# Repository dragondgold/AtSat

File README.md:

<h2>
</a>Desarrollo de satélite CanSat para
utilizar como plataforma educativa y
fomentar el interés en ingenierías</h2>

El objetivo principal del proyecto es el de proveer un satélite tipo CanSat completamente funcional y listo para ser utilizado, 
con una Estación Terrena para la comunicación con el mismo, a modo de plataforma educativa que permite no solo ser utilizada 
por estudiantes sin modificación alguna, sino que provee la capacidad de ser expandida para agregar o mejorar las funcionalidades 
básicas dando lugar a los estudiantes a experimentar libremente sobre una plataforma segura.

A su vez, la plataforma sera diseñada siguiendo la normativa impuesta por la European Space Agency (ESA) 
lo cual dará la posibilidad a futuro de participar de competencias de CanSat.

El proyecto está pensado para que el CanSat pueda alcanzar una altura máxima de
1000 metros aproximadamente y realice un descenso con la ayuda de un paracaídas que
limitará su velocidad para evitar la destrucción del mismo al impactar contra el suelo.
Durante esta etapa también se realizará la medición de las variables
que envía el CanSat a la Estación Terrena para luego ser interpretadas. Esto permite
analizar diversos factores respecto a la altura como los niveles de contaminación del
aire, la variabilidad de la temperatura y presión atmosférica, la toma de imágenes para
su posterior procesamiento, medición de radiación UV, composición gaseosa del aire,
etcétera.

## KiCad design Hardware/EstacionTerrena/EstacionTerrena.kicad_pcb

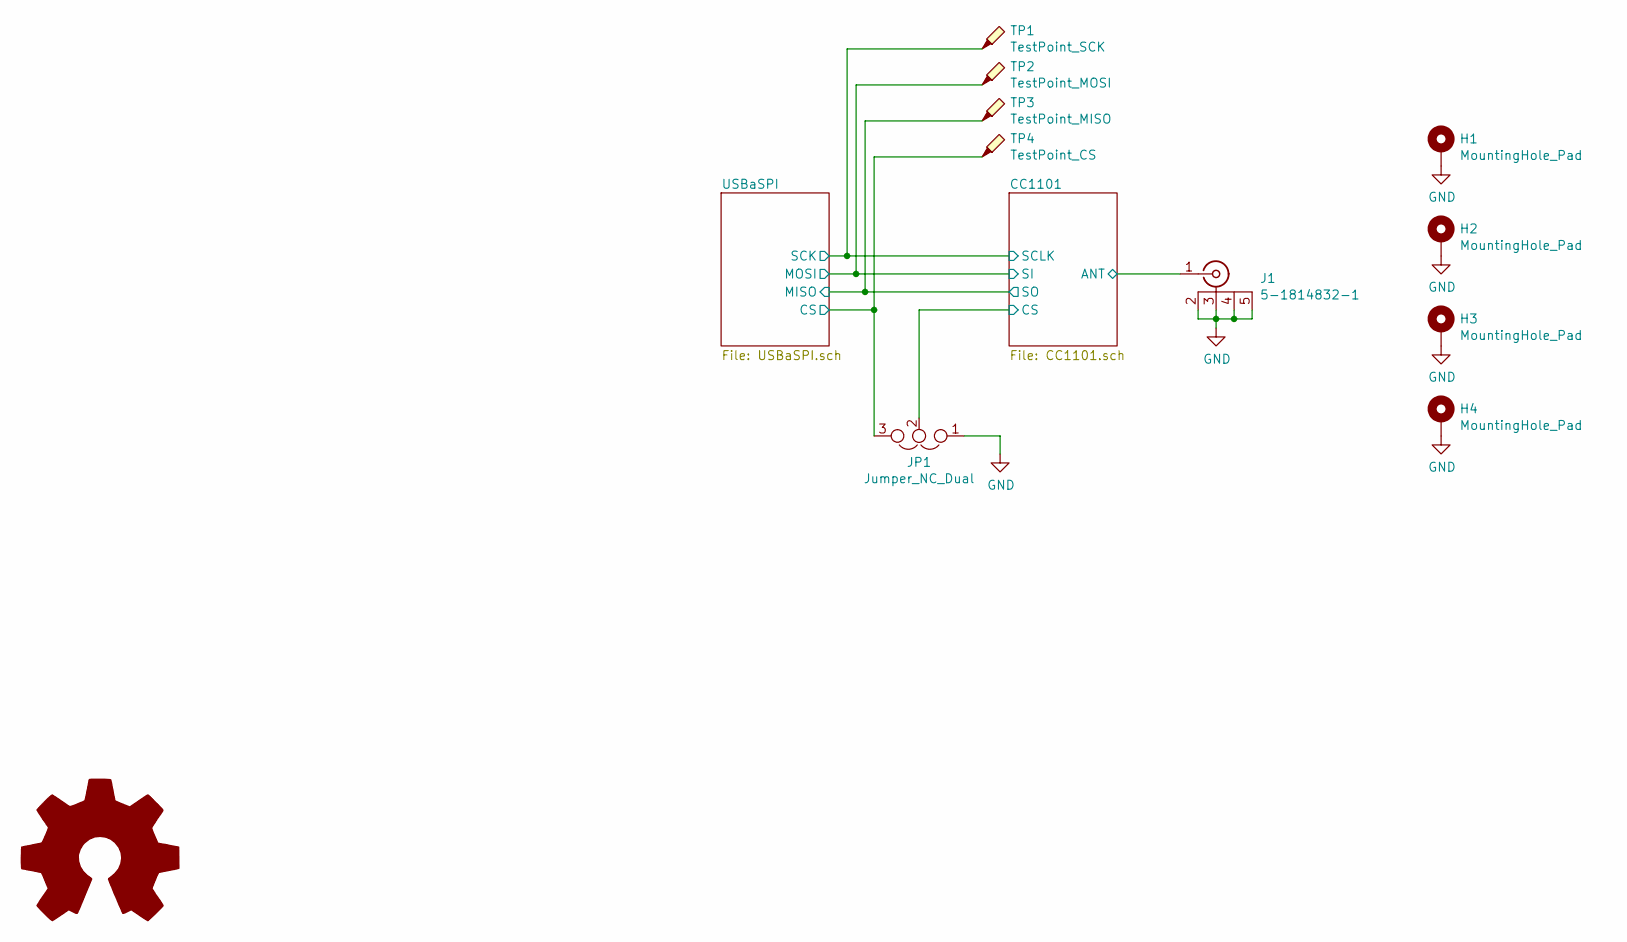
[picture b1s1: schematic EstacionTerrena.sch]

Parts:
H1, H2, H3, H4: MountingHole_Pad; MountingHole_3.2mm_M3_Pad
J1: 5-1814832-1; Manufacturer Part Number 5-1814832-1
JP1: Jumper_NC_Dual; SolderJumper-3_P1.3mm_Open_RoundedPad1.0x1.5mm_NumberLabels
TP1: TestPoint_SCK; TestPoint_Pad_D1.0mm
TP2: TestPoint_MOSI; TestPoint_Pad_D1.0mm
TP3: TestPoint_MISO; TestPoint_Pad_D1.0mm
TP4: TestPoint_CS; TestPoint_Pad_D1.0mm

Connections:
/CC1101/ANT: J1.1; also elsewhere on the board
/CC1101/CS: JP1.2; also elsewhere on the board
/USBaSPI/CS: JP1.3, TP4.1; also elsewhere on the board
/USBaSPI/MISO: TP3.1; also elsewhere on the board
/USBaSPI/MOSI: TP2.1; also elsewhere on the board
/USBaSPI/SCK: TP1.1; also elsewhere on the board
GND: H1.1, H2.1, H3.1, H4.1, J1.2, J1.3, J1.4, J1.5, JP1.1; also elsewhere on the board

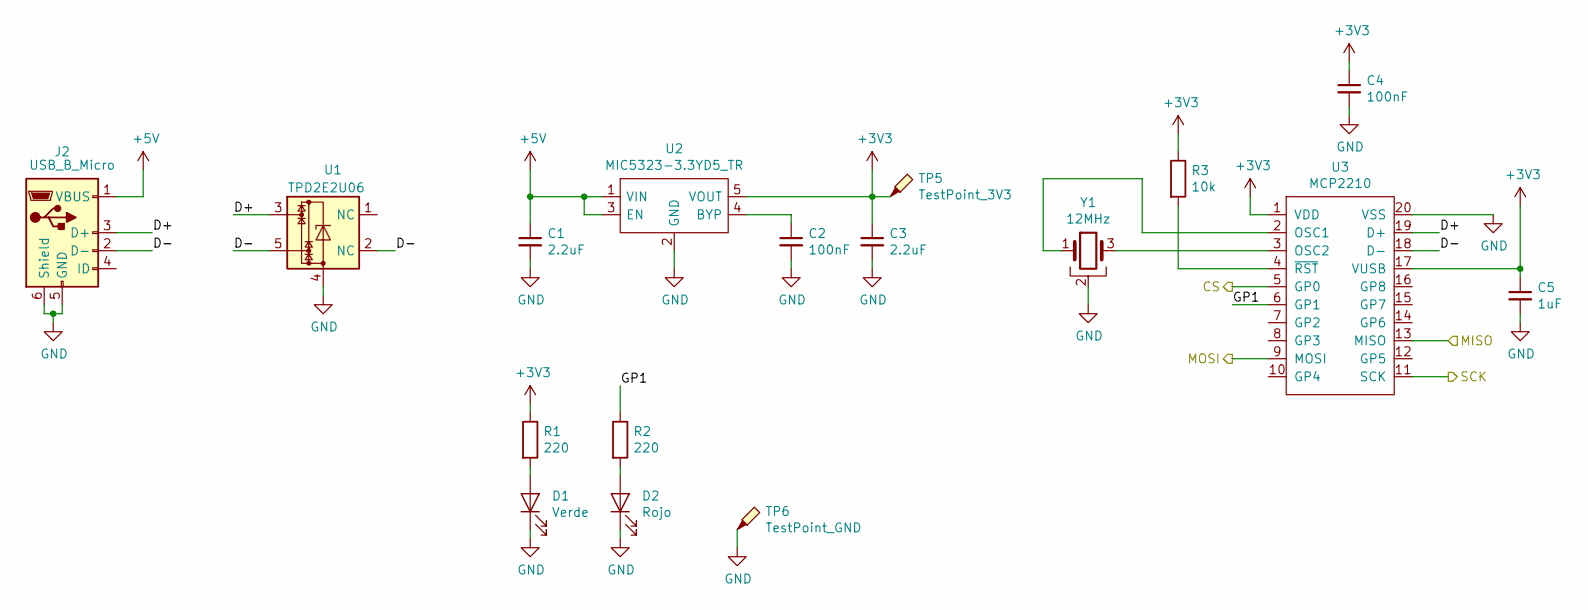
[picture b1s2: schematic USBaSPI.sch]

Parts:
C1, C3: 2.2uF; C_0805_2012Metric; Voltage 10V; Manufacturer Part Number LMK212B7225KG-T
C2, C4: 100nF; C_0603_1608Metric; Voltage 16V; Manufacturer Part Number EMK107B7104KAHT
C5: 1uF; C_0603_1608Metric; Voltage 10V; Manufacturer Part Number LMK107B7105MA-T
D1: Verde; LED_0603_1608Metric; Manufacturer Part Number 150060VS75000
D2: Rojo; LED_0603_1608Metric; Manufacturer Part Number 150060RS75000
J2: USB_B_Micro; USB_Micro-B_Molex-105017-0001; Manufacturer Part Number 105017-0001
R1, R2: 220; R_0603_1608Metric_Pad1.05x0.95mm_HandSolder; Manufacturer Part Number RC0603JR-13220RL
R3: 10k; R_0603_1608Metric_Pad1.05x0.95mm_HandSolder; Manufacturer Part Number RC0603JR-0710KL
TP5: TestPoint_3V3; TestPoint_Pad_D1.0mm
TP6: TestPoint_GND; TestPoint_THTPad_1.0x1.0mm_Drill0.5mm
U1: TPD2E2U06; SOT-553; Manufacturer Part Number TPD2E2U06DRLR
U2: MIC5323-3.3YD5_TR; SOT95P280X100-5N; Manufacturer Part Number MIC5323-3.3YD5 TR
U3: MCP2210; SSOP-20_5.3x7.2mm_P0.65mm; Manufacturer Part Number MCP2210-I/SS
Y1: 12MHz; Resonator_SMD_muRata_CSTxExxV-3Pin_3.0x1.1mm; Manufacturer Part Number CSTNE12M0GH5L000R0

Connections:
+3V3: C3.1, C4.1, C5.1, R1.1, R3.1, TP5.1, U2.5 (VOUT), U3.1 (VDD), U3.17 (VUSB); also elsewhere on the board
+5V: C1.1, J2.1 (VBUS), U2.1 (VIN), U2.3 (EN)
/USBaSPI/CS: U3.5 (GP0); also elsewhere on the board
/USBaSPI/D+: J2.3 (D+), U1.3, U3.19 (D+)
/USBaSPI/D-: J2.2 (D-), U1.2 (NC), U1.5, U3.18 (D-)
/USBaSPI/GP1: R2.1, U3.6 (GP1)
/USBaSPI/MISO: U3.13 (MISO); also elsewhere on the board
/USBaSPI/MOSI: U3.9 (MOSI); also elsewhere on the board
/USBaSPI/SCK: U3.11 (SCK); also elsewhere on the board
GND: C1.2, C2.2, C3.2, C4.2, C5.2, D1.1 (K), D2.1 (K), J2.5 (GND), J2.6 (Shield), TP6.1, U1.4, U2.2 (GND), U3.20 (VSS), Y1.2; also elsewhere on the board
unnamed: C2.1, U2.4 (BYP)
unnamed: D1.2 (A), R1.2
unnamed: D2.2 (A), R2.2
unnamed: R3.2, U3.4 (~RST)
unnamed: U3.2 (OSC1), Y1.1
unnamed: U3.3 (OSC2), Y1.3

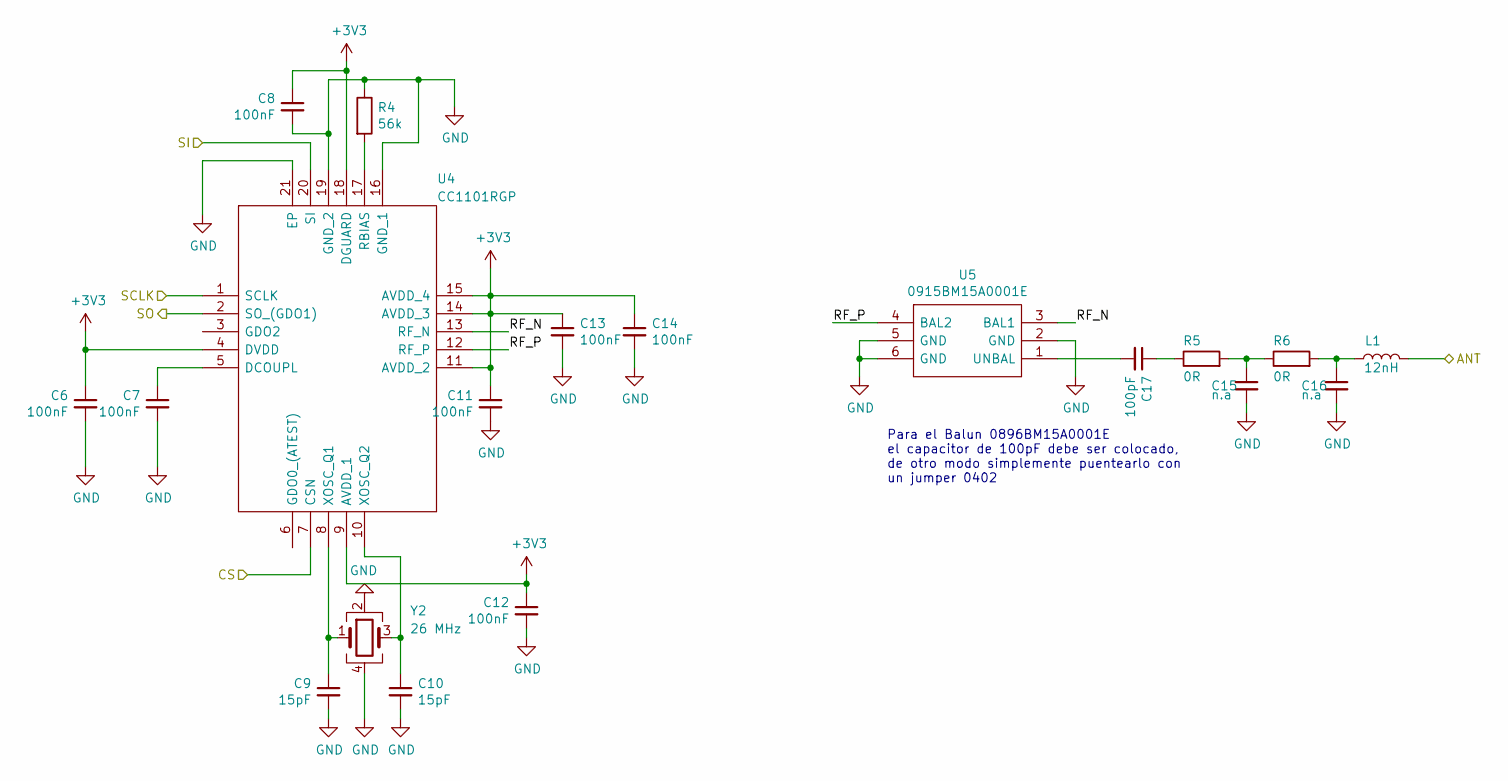
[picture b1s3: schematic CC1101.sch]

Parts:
C6, C7, C8, C11, C12, C13, C14: 100nF; C_0402_1005Metric; Voltage 16V; Manufacturer Part Number GCM155R71C104KA55D
C9, C10: 15pF; C_0402_1005Metric; Voltage 10V; Manufacturer Part Number C0402C150J5GACTU
C15, C16: n.a; C_0402_1005Metric
C17: 100pF; C_0402_1005Metric; Voltage 25V; Manufacturer Part Number 885012005046
L1: 12nH; L_0402_1005Metric; Manufacturer Part Number L-07C12NJV6
R4: 56k; R_0402_1005Metric; Manufacturer Part Number RC0402FR-0756KL
R5, R6: 0R; R_0402_1005Metric; Manufacturer Part Number RC0402JR-070RL
U4: CC1101RGP; QFN50P400X400X100-21N-D; Manufacturer Part Number CC1101RGP
U5: 0915BM15A0001E; Manufacturer Part Number 0915BM15A0001E
Y2: 26 MHz; Crystal_SMD_2520-4Pin_2.5x2.0mm; Manufacturer Part Number FA-20H 26.0000MF12V-W

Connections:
+3V3: C6.1, C8.1, C11.1, C12.1, C13.1, C14.1, U4.4 (DVDD), U4.9 (AVDD_1), U4.11 (AVDD_2), U4.14 (AVDD_3), U4.15 (AVDD_4), U4.18 (DGUARD); also elsewhere on the board
/CC1101/ANT: L1.2; also elsewhere on the board
/CC1101/CS: U4.7 (CSN); also elsewhere on the board
/CC1101/RF_N: U4.13 (RF_N), U5.3 (BAL1)
/CC1101/RF_P: U4.12 (RF_P), U5.4 (BAL2)
/USBaSPI/MISO: U4.2 (SO_(GDO1)); also elsewhere on the board
/USBaSPI/MOSI: U4.20 (SI); also elsewhere on the board
/USBaSPI/SCK: U4.1 (SCLK); also elsewhere on the board
GND: C6.2, C7.2, C8.2, C9.2, C10.2, C11.2, C12.2, C13.2, C14.2, C15.2, C16.2, R4.1, U4.16 (GND_1), U4.19 (GND_2), U4.21 (EP), U5.2 (GND), U5.5 (GND), U5.6 (GND), Y2.2, Y2.4; also elsewhere on the board
unnamed: C7.1, U4.5 (DCOUPL)
unnamed: C9.1, U4.8 (XOSC_Q1), Y2.1
unnamed: C10.1, U4.10 (XOSC_Q2), Y2.3
unnamed: C15.1, R5.2, R6.1
unnamed: C16.1, L1.1, R6.2
unnamed: C17.1, R5.1
unnamed: C17.2, U5.1 (UNBAL)
unnamed: R4.2, U4.17 (RBIAS)

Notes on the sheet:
Para el Balun 0896BM15A0001E el capacitor de 100pF debe ser colocado, de otro modo simplemente puentearlo con un jumper 0402

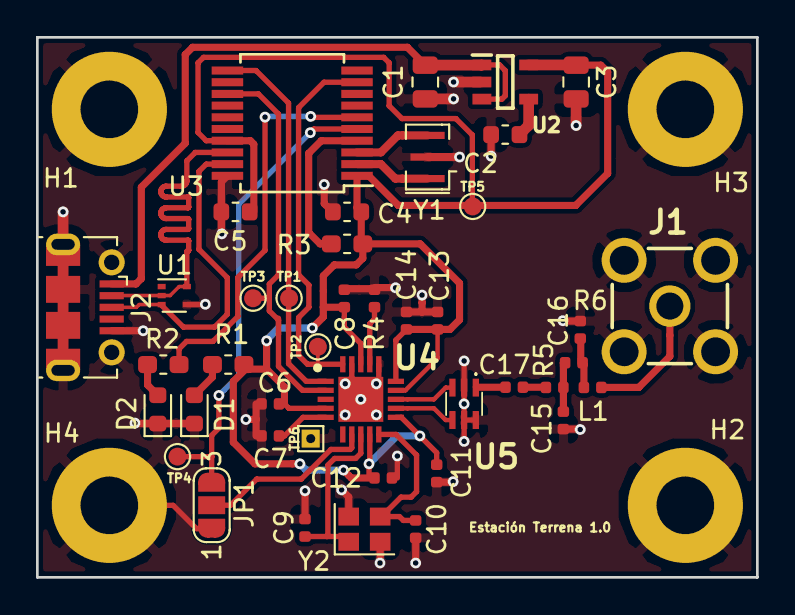
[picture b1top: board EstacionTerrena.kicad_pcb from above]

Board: 2 copper layers, 40.0 x 30.0 mm, 46 parts (0 on the bottom side), 28 nets.

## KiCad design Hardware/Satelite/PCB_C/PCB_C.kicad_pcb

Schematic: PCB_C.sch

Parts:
C1, C13: 1uF; C_0402_1005Metric; Manufacturer Part Number GRM155R61E105KA12D
C2, C5, C6, C9, C10, C11, C12, C14, C18, C19, C21: 100nF; C_0402_1005Metric; Manufacturer Part Number GCM155R71C104KA55D
C3, C4: 4.3pF; C_0402_1005Metric; Manufacturer Part Number GRM1555C1H4R3WA01D
C7, C8: 20pF; C_0402_1005Metric; Manufacturer Part Number GCM1555C1H200JA16D
C20: 4.7uF; C_0805_2012Metric_Pad1.15x1.40mm_HandSolder; Manufacturer Part Number GRM21BR71A475KE51K
IC1: MCP1501T-33E_CHY; SOT95P270X145-6N; Manufacturer Part Number MCP1501T-33E/CHY
IC2: IS25LP080D-JULE-TR; SON50P200X300X60-8N; Manufacturer Part Number IS25LP080D-JULE-TR
IC3: BQ24392RSER; RSE(R-PUQFN-N10); Manufacturer Part Number BQ24392RSER
J1: Conn_01x06; PinHeader_1x06_P2.54mm_Vertical; Manufacturer Part Number 68000-406HLF
J2: BOOT; PinHeader_1x03_P2.54mm_Vertical; Manufacturer Part Number 61300311121
J3: Conector_PCB_B-C; Conector_PCB_B-C_Lado_C; Manufacturer Part Number 10132797-025100LF
J4: Conector_Expansion_CanSat; Manufacturer Part Number SSQ-106-03-T-S
J5: USB_B_Micro; USB_Micro-B_Molex-105017-0001; Manufacturer Part Number 105017-0001
JP1: BOM_Jumper; Empty_Footprint; Manufacturer Part Number M7581-05
M1, M2, M3: Spacer; Empty_Footprint; Manufacturer Part Number R30-3011002
MH1: MH_CanSat
R1, R2, R3, R4: 10k; R_0603_1608Metric_Pad1.05x0.95mm_HandSolder; Manufacturer Part Number RC0603JR-0710KL
U1, U4: NTB0104BQ,115; NTB0104BQ115; Manufacturer Part Number NTB0104BQ,115
U2: TCA9802DGKR; SOP65P490X110-8N; Manufacturer Part Number TCA9802DGKR
U3: STM32F303RETx; LQFP-64_10x10mm_P0.5mm
Y1: LFXTAL016178; LFXTAL016178_1; Manufacturer Part Number LFXTAL016178
Y2: Crystal; Crystal_HC49-4H_Vertical; Manufacturer Part Number LFXTAL029665

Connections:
+3V3: C5.1, C11.1, C21.1, J3.4, J3.17, J4.14, U1.14, U2.8, U4.14; also elsewhere on the board
+3V3_Internal: C2.1, C9.1, C10.1, C12.1, C13.2, C14.1, C18.1, C19.1, C20.2, IC2.3, IC2.7, IC2.8, J1.1, J2.3, J3.10, R1.1, R2.1, R3.1, R4.1, U1.1, U2.1, U3.1 (VBAT), U3.19 (VDD), U3.32 (VDD), U3.48 (VDD), U3.64 (VDD), U4.1
+5V: J3.5, J3.13, J4.15
+BATT: C1.2, IC1.4, IC1.6, J3.6, J3.7, J3.8, J3.9, J4.13
/3V_ENABLE: J3.18, U3.26 (PB0)
/5V_ENABLE: J3.14, U3.23 (PA7)
/+VREF: IC1.1, U3.13 (VDDA)
/CHG: J3.29, U3.61 (PB8)
/CHG_ALLOWED: IC3.4, U3.27 (PB1)
/CHG_DETECT: IC3.10, U3.16 (PA2)
/CHG_DISABLE: J3.28, U3.54 (PD2)
/CS: J3.36, U3.33 (PB12), U4.5
/D+: IC3.3, U3.45 (PA12)
/D-: IC3.2, U3.44 (PA11)
/EXT_CS: J4.22, U4.10
/EXT_IO0: J4.3, U1.13
/EXT_IO1: J4.4, U1.12
/EXT_IO2: J4.5, U1.11
/EXT_IO3: J4.6, U1.10
/EXT_SCLK: J4.21, U4.11
/EXT_SDI: J4.20, U4.12
/EXT_SDO: J4.19, U4.13
/FLASH_CS: IC2.1, U3.2 (PC13)
/FLASH_MISO: IC2.2, U3.52 (PC11)
/FLASH_MOSI: IC2.5, U3.53 (PC12)
/FLASH_SCK: IC2.6, U3.51 (PC10)
/GPOUT: J3.24, U3.57 (PB5)
/GPS_TX: J3.20, U3.56 (PB4)
/I2C_EN: U2.5, U3.24 (PC4)
/IO0: U1.2, U3.10 (PC2)
/IO1: U1.3, U3.11 (PC3)
/IO2: U1.4, U3.29 (PB10)
/IO3: U1.5, U3.30 (PB11)
/IO_EN: U1.8, U3.39 (PC8)
/ISET: J3.30, U3.62 (PB9)
/I_SENSE_3V3: J3.16, U3.15 (PA1)
/I_SENSE_5V: J3.12, U3.14 (PA0)
/I_SENSE_BATT: J3.31, U3.17 (PA3)
/NRST: C6.1, J1.5, U3.7 (NRST)
/P1: J3.19, U3.59 (PB7)
/SCL: R3.2, U2.3, U3.42 (PA9); also elsewhere on the board
/SCLK: J3.35, U3.34 (PB13), U4.4
/SCL_CHG: J3.25, R2.2, U3.41 (PA8)
/SCL_EXT: J4.23, U2.6
/SDA: R4.2, U2.2, U3.43 (PA10); also elsewhere on the board
/SDA_CHG: J3.26, R1.2, U3.40 (PC9)
/SDA_EXT: J4.24, U2.7
/SDI: J3.37, U3.36 (PB15), U4.3
/SDO: J3.34, U3.35 (PB14), U4.2
/SPI_BUFFER_EN: U3.25 (PC5), U4.8
/SWCLK: J1.2, U3.49 (PA14)
/SWDIO: J1.4, U3.46 (PA13)
/SWO: J1.6, U3.55 (PB3)
/SW_OPEN: IC3.1, U3.28 (PB2)
/S_GLOBO: J3.32, U3.8 (PC0)
/S_PARACAIDAS: J3.33, U3.9 (PC1)
/V_SENSE_3V3: J3.15, U3.20 (PA4)
/V_SENSE_5V: J3.11, U3.21 (PA5)
GND: C1.1, C2.2, C3.2, C4.2, C5.2, C6.2, C7.2, C8.2, C9.2, C10.2, C11.2, C12.2, C13.1, C14.2, C18.2, C19.2, C20.1, C21.2, IC1.2, IC1.3, IC1.5, IC2.4, IC3.6, J1.3, J2.1, J3.1, J3.2, J3.3, J3.21, J3.22, J3.23, J3.38, J3.39, J3.40, J4.16, J4.17, J4.18, J5.5, J5.6, MH1.1, MH1.2, MH1.3, U1.7, U1.15, U2.4, U3.12 (VSSA), U3.18 (VSS), U3.31 (VSS), U3.47 (VSS), U3.63 (VSS), U4.7, U4.15; also elsewhere on the board
unnamed: C3.1, U3.3 (PC14), Y1.1
unnamed: C4.1, U3.4 (PC15), Y1.4
unnamed: C7.1, U3.5 (PF0), Y2.1
unnamed: C8.1, U3.6 (PF1), Y2.2
unnamed: IC3.7, J5.3
unnamed: IC3.8, J5.2
unnamed: J2.2, U3.60 (BOOT0)
VBUS: IC3.5, IC3.9, J3.27, J5.1

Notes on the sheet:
USB y detección de cargador
Sensores
+VREF ADC
Header programación
Buffer SPI
Buffer I2C
Buffer IO_A
Conectores a PCB_B
Conector de expansión
AGUJEROS DE MONTAJE
Mecánica

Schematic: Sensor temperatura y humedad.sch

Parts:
C22: 100nF; C_0402_1005Metric; Manufacturer Part Number GCM155R71C104KA55D
U6: Si7006-A20-IM1; SON100P300X300X80-7N; Manufacturer Part Number Si7006-A20-IM1

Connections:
+3V3: C22.1, U6.5; also elsewhere on the board
/SCL: U6.6; also elsewhere on the board
/SDA: U6.1; also elsewhere on the board
GND: C22.2, U6.2; also elsewhere on the board

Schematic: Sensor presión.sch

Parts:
C23: 1uF; C_0402_1005Metric; Manufacturer Part Number GRM155R61E105KA12D
IC4: MS563702BA03-50; MS5637_1; Manufacturer Part Number MS563702BA03-50

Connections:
+3V3: C23.2, IC4.1; also elsewhere on the board
/SCL: IC4.3; also elsewhere on the board
/SDA: IC4.2; also elsewhere on the board
GND: C23.1, IC4.4; also elsewhere on the board

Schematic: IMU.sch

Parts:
C24, C25: 100nF; C_0402_1005Metric; Manufacturer Part Number GCM155R71C104KA55D
IC5: BMX055; LGA_PACKAGE_20_PINS; Manufacturer Part Number BMX055

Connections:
+3V3: C24.1, C25.1, IC5.3, IC5.7, IC5.13; also elsewhere on the board
/IMU/ACC_INT: IC5.1
/IMU/GYRO_INT: IC5.14
/IMU/MAG_INT: IC5.10
/SCL: IC5.9; also elsewhere on the board
/SDA: IC5.11; also elsewhere on the board
GND: C24.2, C25.2, IC5.4, IC5.6, IC5.12, IC5.17, IC5.20; also elsewhere on the board

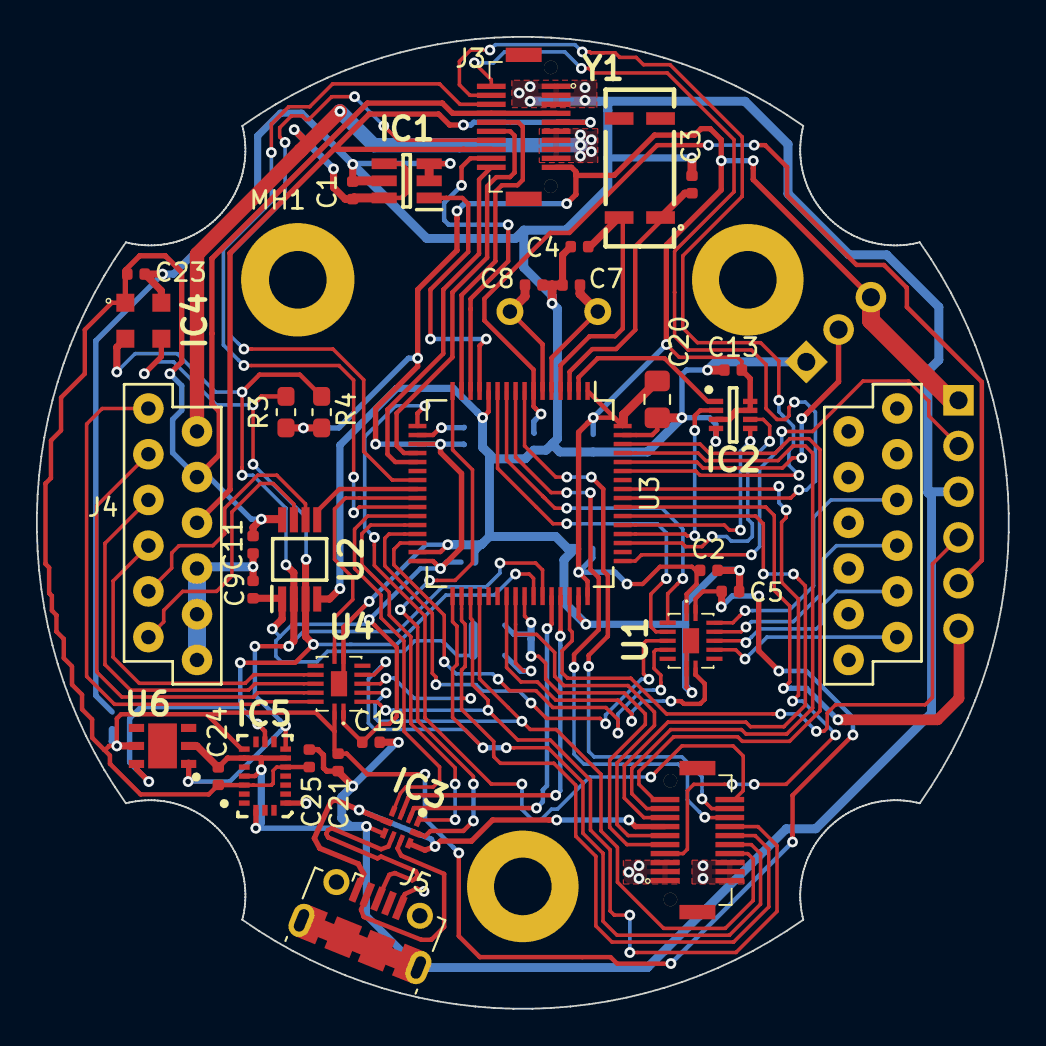
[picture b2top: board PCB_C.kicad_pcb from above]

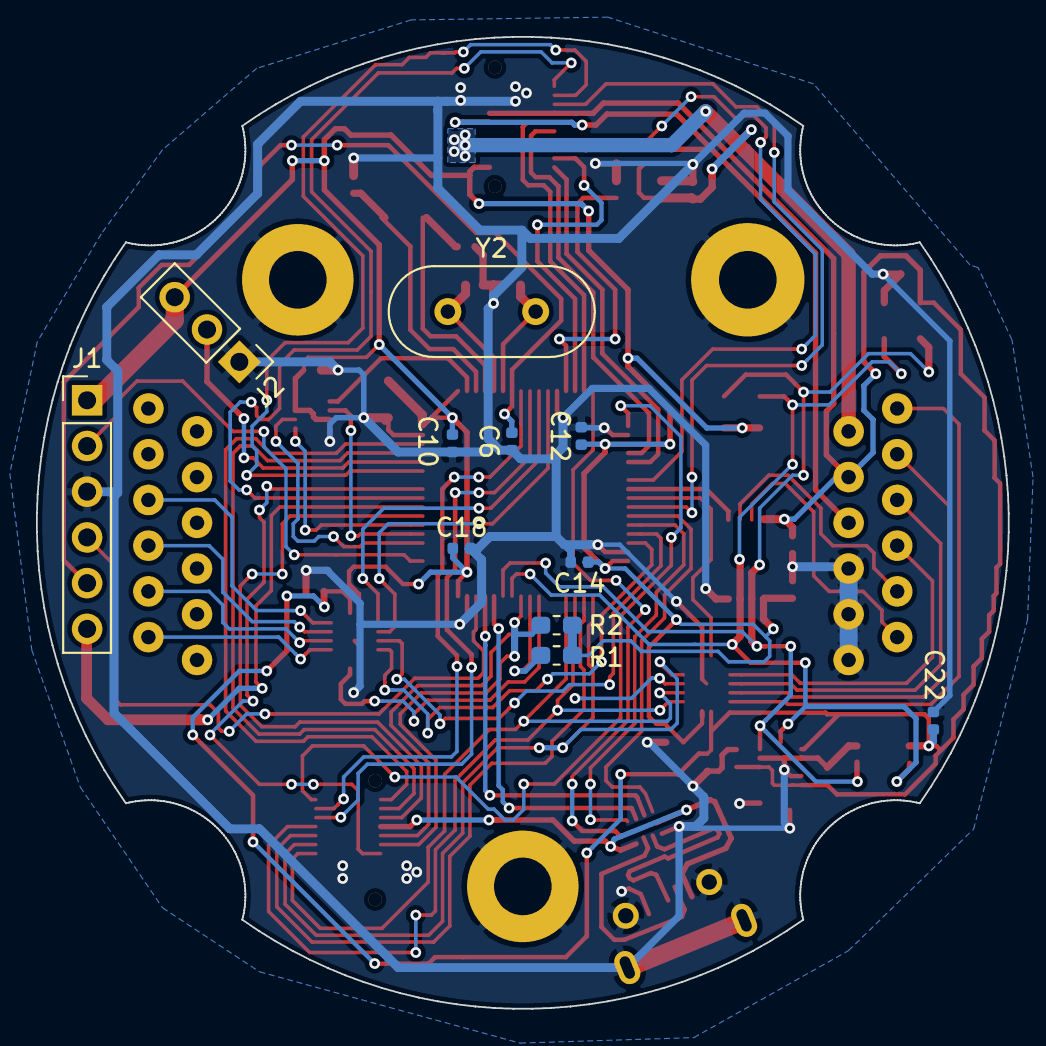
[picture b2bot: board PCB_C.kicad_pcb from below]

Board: 2 copper layers, 54.0 x 54.0 mm, 48 parts (11 on the bottom side), 67 nets.

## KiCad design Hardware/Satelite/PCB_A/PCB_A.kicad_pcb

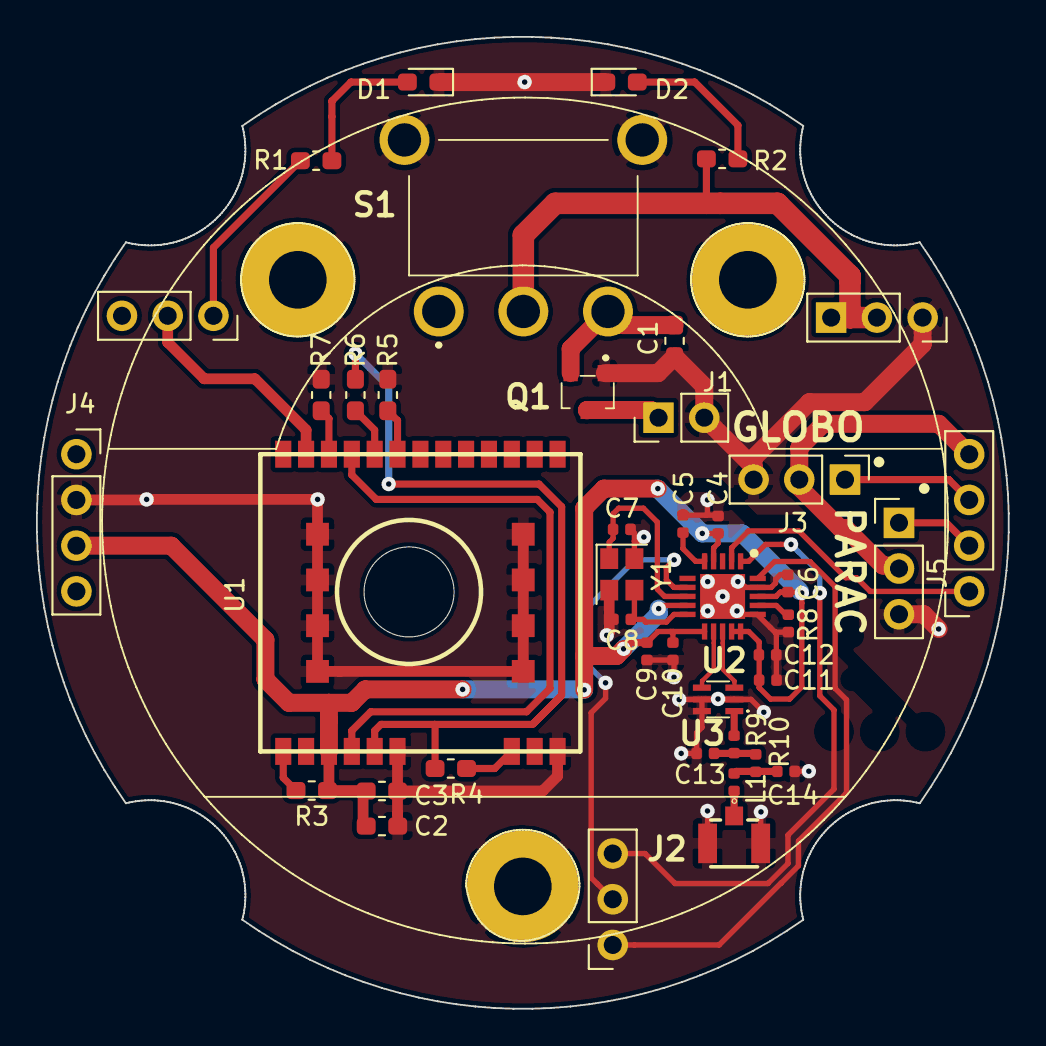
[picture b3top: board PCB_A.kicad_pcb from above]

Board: 2 copper layers, 54.0 x 54.0 mm, 42 parts (0 on the bottom side), 33 nets.

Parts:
C1, C3: 1uF; C_0603_1608Metric_Pad1.05x0.95mm_HandSolder
C2: 100nF; C_0603_1608Metric_Pad1.05x0.95mm_HandSolder
C4, C5, C6, C9, C10, C11, C12: 100nF; C_0402_1005Metric
C7, C8: 18pF; C_0402_1005Metric
C13, C14: n.a; C_0402_1005Metric
D1: Rojo; LED_0603_1608Metric_Pad1.05x0.95mm_HandSolder
D2: Verde; LED_0603_1608Metric_Pad1.05x0.95mm_HandSolder
J1: Batería LiPo (Soldada); PinHeader_1x02_P2.54mm_Vertical
J2: CONUFL001-SMD
J3: Servo Globo; PinHeader_1x03_P2.54mm_Vertical
J4: Conector_PCB_A-B
J5: Servo Paracaídas; PinHeader_1x03_P2.54mm_Vertical
L1: 12nH; L_0402_1005Metric
M1, M2, M3: Spacer; Empty_Footprint
MH1: MH_CanSat
Q1: SSM3J338R,LF; SSM3J332RLFT
R1, R2: 1k; R_0603_1608Metric_Pad1.05x0.95mm_HandSolder
R3, R4, R5, R6, R7: 10k; R_0603_1608Metric_Pad1.05x0.95mm_HandSolder
R8: 56k; R_0402_1005Metric
R9, R10: 0R; R_0402_1005Metric
S1: 500SSP1S1M6QEA
U1: A2235-H
U2: CC1101RGP; QFN50P400X400X100-21N-D
U3: 0915BM15A0001E
Y1: 26 MHz; Crystal_SMD_2520-4Pin_2.5x2.0mm

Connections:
+3V3_Internal: C2.1, C3.1, C4.1, C6.1, C9.1, C10.1, C11.1, C12.1, J4.16, R3.1, U1.3, U2.4, U2.9, U2.11, U2.14, U2.15, U2.18
+5V: J3.2, J4.4, J5.2
+BATT: C1.1, Q1.2, S1.3
/CC1101/ANT: J2.1, L1.2
/CC1101/RF_N: U2.13, U3.3
/CC1101/RF_P: U2.12, U3.4
/CS: J4.9, U2.7
/GPS/GPS_1V8: R4.1, R6.2, U1.5
/GPS_TX: J4.12, U1.21
/P1: J4.11, R1.1
/SCLK: J4.10, U2.1
/SDI: J4.8, U2.20
/SDO: J4.7, U2.2
/S_GLOBO: J3.1, J4.5
/S_PARACAIDAS: J4.6, J5.1
GND: C1.2, C2.2, C3.2, C4.2, C5.2, C6.2, C7.2, C8.2, C9.2, C10.2, C11.2, C12.2, C13.2, C14.2, D1.1, D2.1, J1.2, J2.2, J2.3, J3.3, J4.3, J4.15, J5.3, MH1.1, MH1.2, MH1.3, Q1.1, R5.2, R7.2, R8.1, S1.4, S1.5, U1.6, U1.9, U1.23, U1.24, U1.25, U1.26, U1.27, U1.28, U1.29, U1.30, U2.16, U2.19, U2.21, U3.2, U3.5, U3.6, Y1.2, Y1.4
unnamed: C5.1, U2.5
unnamed: C7.1, U2.8, Y1.1
unnamed: C8.1, U2.10, Y1.3
unnamed: C13.1, R9.2, R10.1
unnamed: C14.1, L1.1, R10.2
unnamed: D1.2, R1.2
unnamed: D2.2, R2.2
unnamed: J1.1, Q1.3
unnamed: J4.1, J4.2, R2.1, S1.2
unnamed: R3.2, U1.1
unnamed: R4.2, U1.7
unnamed: R5.1, U1.17
unnamed: R6.1, U1.18
unnamed: R7.1, U1.20
unnamed: R8.2, U2.17
unnamed: R9.1, U3.1
unnamed: U1.4, U1.19

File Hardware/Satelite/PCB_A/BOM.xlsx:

Component | Description | Part | References | Value | Footprint | Quantity Per PCB | Manufacturer Part Number
1 | Unpolarized capacitor, small symbol | C_Small | C4 C5 C6 C9 C10 C11 C12 | 100nF | C_0402_1005Metric | 7 | GCM155R71C104KA55D
2 | Unpolarized capacitor, small symbol | C_Small | C2 | 100nF | C_0603_1608Metric_Pad1.05x0.95mm_HandSolder | 1 | GCM155R71C104KA55D
3 | Unpolarized capacitor, small symbol | C_Small | C7 C8 | 15pF | C_0402_1005Metric | 2 | C0402C150J5GACTU
4 | Unpolarized capacitor, small symbol | C_Small | C1 C3 | 1uF | C_0603_1608Metric_Pad1.05x0.95mm_HandSolder | 2 | LMK107B7105MA-T
6 | Light emitting diode | LED | D1 | Rojo | LED_0603_1608Metric_Pad1.05x0.95mm_HandSolder | 1 | 150060RS75000
7 | Light emitting diode | LED | D2 | Verde | LED_0603_1608Metric_Pad1.05x0.95mm_HandSolder | 1 | 150060RS75000
9 | RF Connectors / Coaxial Connectors U.FL Straight Surface Mount Jack | CONUFL001-SMD | J2 | CONUFL001-SMD | CONUFL001-SMD | 1 | CONUFL001-SMD
10 |  | Conector_PCB_A-B | J4 | Conector_PCB_A-B | Conector_PCB_A-B | 3 | 61300311121
11 |  |  | J4 | Conector_PCB_A-B | Conector_PCB_A-B | 2 | 61300411121
12 | Generic connector, single row, 01x03, script generated (kicad-library-utils/sch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 | Conn_01x03 | J3 | Servo Globo | PinHeader_1x03_P2.54mm_Vertical | 1 | 61300311121
13 | Generic connector, single row, 01x03, script generated (kicad-library-utils/sch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 | Conn_01x03 | J5 | Servo ParacaÃ­das | PinHeader_1x03_P2.54mm_Vertical | 1 | 61300311121
14 | Inductor | L | L1 | 12nH | L_0402_1005Metric | 1 | L-07C12NJV6
15 |  | Spacer | M1 M2 M3 | Spacer | Empty_Footprint | 3 | R30-3011002
17 | MOSFET Small-signal MOSFET Vdss= -12V, ID= -6A | SSM3J338R,LF | Q1 | SSM3J338R,LF | SSM3J332RLFT | 1 | SSM3J338R,LF
18 | Resistor | R | R9 R10 | 0R | R_0402_1005Metric | 2 | RC0402JR-070RL
19 | Resistor | R | R3 R4 R5 R6 R7 | 10k | R_0603_1608Metric_Pad1.05x0.95mm_HandSolder | 5 | RC0603JR-0710KL
20 | Resistor | R | R1 R2 | 1k | R_0603_1608Metric_Pad1.05x0.95mm_HandSolder | 2 | RC0603JR-071KL
21 | Resistor | R | R8 | 56k | R_0402_1005Metric | 1 | RC0402FR-0756KL
22 | Slide Switches SPDT RA SLIDE PC MNT | 500SSP1S1M6QEA | S1 | 500SSP1S1M6QEA | 500SSP1S1M6QEA | 1 | 500SSP1S1M6QEA
23 | Signal Conditioning 915MHz BALUN/FILTER | 0915BM15A0001E | U3 | 0915BM15A0001E | 0915BM15A0001E | 1 | 0915BM15A0001E
24 | GPS Modules SiRFStarIV GPS receiver SMT ROM mod | A2235-H | U1 | A2235-H | A2235-H | 1 | A2235-H
25 | Texas Instruments CC1101RGP, RF Transceiver IC Triple Band 1.8 3.6 V 20-Pin QFN | CC1101RGP | U2 | CC1101RGP | QFN50P400X400X100-21N-D | 1 | CC1101RGP
26 | Four pin crystal, GND on pins 2 and 4 | Crystal_GND24 | Y1 | 26 MHz | Crystal_SMD_2520-4Pin_2.5x2.0mm | 1 | FA-20H 26.0000MF12V-W

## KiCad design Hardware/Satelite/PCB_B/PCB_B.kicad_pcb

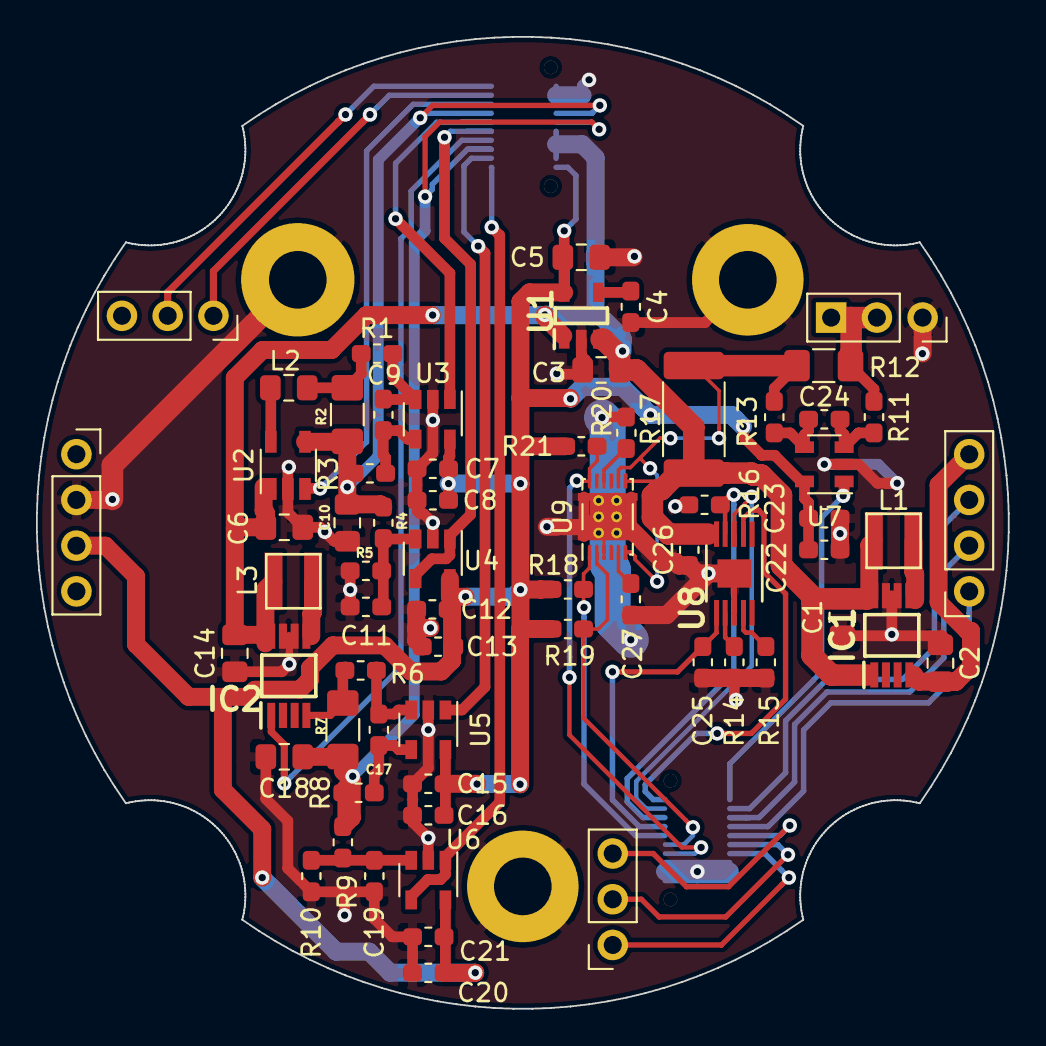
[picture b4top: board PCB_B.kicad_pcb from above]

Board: 2 copper layers, 54.0 x 54.0 mm, 65 parts (0 on the bottom side), 48 nets.

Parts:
C1, C2, C6, C10, C14, C18: 10uF; C_0805_2012Metric_Pad1.15x1.40mm_HandSolder
C3, C5: 2.2uF; C_0805_2012Metric_Pad1.15x1.40mm_HandSolder
C4, C7, C11, C13, C15, C21, C22: 100nF; C_0603_1608Metric_Pad1.05x0.95mm_HandSolder
C8, C9, C12, C16, C17, C20, C23, C24, C25, C26: 1uF; C_0603_1608Metric_Pad1.05x0.95mm_HandSolder
C19: 10n; C_0603_1608Metric_Pad1.05x0.95mm_HandSolder
C27: 0.47uF; C_0603_1608Metric_Pad1.05x0.95mm_HandSolder
IC1, IC2: MCP1642B-50I_MS; SOP65P490X110-8N
J1: Conector_PCB_B-C; Conector_PCB_B-C_Lado_B
J2: Conector_PCB_A-B
L1, L3: 4.7uH; SRN3010TA-4R7M
L2: 1uH; L_0805_2012Metric_Pad1.15x1.40mm_HandSolder
MH1: MH_CanSat
R1, R3, R6, R8, R11, R13: 51R; R_0603_1608Metric_Pad1.05x0.95mm_HandSolder
R2: 120m; R_1206_3216Metric_Pad1.42x1.75mm_HandSolder
R4, R15: 2k; R_0603_1608Metric_Pad1.05x0.95mm_HandSolder
R5: 130k; R_0603_1608Metric_Pad1.05x0.95mm_HandSolder
R7: 200m; R_1206_3216Metric_Pad1.42x1.75mm_HandSolder
R9: 22k; R_0603_1608Metric_Pad1.05x0.95mm_HandSolder
R10: 39k; R_0603_1608Metric_Pad1.05x0.95mm_HandSolder
R12: 51m; R_1206_3216Metric_Pad1.42x1.75mm_HandSolder
R14: 1k8; R_0603_1608Metric_Pad1.05x0.95mm_HandSolder
R16: 100k; R_0603_1608Metric_Pad1.05x0.95mm_HandSolder
R17: 10m; R_2512_6332Metric_Pad1.52x3.35mm_HandSolder
R18, R19, R20, R21: 10k; C_0603_1608Metric_Pad1.05x0.95mm_HandSolder
U1: MIC5323-3.3YD5_TR; SOT95P280X100-5N
U2: ADP2108AUJ-3.3; TSOT-23-5
U3, U5, U7: INA194; SOT-23-5
U4, U6: MCP6001-OT; SOT-23-5
U8: BQ24091DGQT; SOP50P490X110-11N
U9: BQ27441DRZR-G1A; Texas_S-PDSO-N12

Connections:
+3V3: C10.2, J1.4, J1.17, R2.1, R3.1, R4.2, U2.4
+3V3_Internal: C5.2, C7.2, C8.2, C12.2, C13.2, C15.2, C16.2, C20.2, C21.2, C22.2, C23.2, J1.10, J2.16, R18.1, R19.1, R21.1, U1.5, U3.5, U4.5, U5.5, U6.5, U7.5
+5V: C18.2, J1.5, J1.13, R7.1, R8.1, R9.2
+BATT: C1.2, C3.2, C6.2, C14.2, C26.2, IC1.1, IC1.8, IC2.8, J1.6, J1.7, J1.8, J1.9, L1.2, L3.2, R17.1, U1.1, U1.3, U2.1, U8.10, U9.7
/BATT_INTERNO: J2.1, J2.2, R11.2, R12.2
/CHG: J1.29, U8.8
/CHG_DISABLE: J1.28, R16.2, U8.9
/CS: J1.36, J2.9
/ENABLE_3V3: J1.18, U2.3
/ENABLE_5V: IC2.1, J1.14
/Fuel Gauge/VBAT: R12.1, R13.2, R17.2, U9.6, U9.8
/GPOUT: J1.24, R21.2, U9.12
/GPS_TX: J1.20, J2.12
/ISET: J1.30, U8.7
/I_SENSE_3V3: J1.16, U3.1
/I_SENSE_5V: J1.12, U5.1
/I_SENSE_BATT: J1.31, U7.1
/P1: J1.19, J2.11
/SCL: J1.25, R19.2, U9.2
/SCLK: J1.35, J2.10
/SDA: J1.26, R18.2, U9.1
/SDI: J1.37, J2.8
/SDO: J1.34, J2.7
/SERVOS_5V: C2.2, IC1.4, J2.4
/S_GLOBO: J1.32, J2.5
/S_PARACAIDAS: J1.33, J2.6
/V_SENSE_3V3: J1.15, U4.1, U4.4
/V_SENSE_5V: J1.11, U6.1, U6.4
GND: C1.1, C2.1, C3.1, C4.1, C5.1, C6.1, C7.1, C8.1, C10.1, C11.1, C12.1, C13.1, C14.1, C15.1, C16.1, C18.1, C19.1, C20.1, C21.1, C22.1, C23.1, C25.1, C26.1, C27.2, IC1.6, IC1.7, IC2.6, IC2.7, J1.1, J1.2, J1.3, J1.21, J1.22, J1.23, J1.38, J1.39, J1.40, J2.3, J2.15, MH1.1, MH1.2, MH1.3, R5.1, R10.1, R14.1, R15.1, R16.1, R20.2, U1.2, U2.2, U3.2, U4.2, U5.2, U6.2, U7.2, U8.3, U8.11, U9.3, U9.13
unnamed: C4.2, U1.4
unnamed: C9.1, R3.2, U3.4
unnamed: C9.2, R1.2, U3.3
unnamed: C11.2, R4.1, R5.2, U4.3
unnamed: C17.1, R8.2, U5.4
unnamed: C17.2, R6.2, U5.3
unnamed: C19.2, R9.1, R10.2, U6.3
unnamed: C24.1, R13.1, U7.4
unnamed: C24.2, R11.1, U7.3
unnamed: C27.1, U9.5
unnamed: IC1.5, L1.1
unnamed: IC2.4, R6.1, R7.2
unnamed: IC2.5, L3.1
unnamed: L2.1, U2.5
unnamed: L2.2, R1.1, R2.2
unnamed: R14.2, U8.2
unnamed: R15.2, U8.4
unnamed: R20.1, U9.10
VBUS: C25.2, J1.27, U8.1

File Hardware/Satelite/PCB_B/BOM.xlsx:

Component | Description | Part | References | Value | Footprint | Quantity Per PCB | Manufacturer Part Number
1 | Unpolarized capacitor, small symbol | C_Small | C27 | 0.47uF | C_0603_1608Metric_Pad1.05x0.95mm_HandSolder | 1 | 885012206024
2 | Unpolarized capacitor, small symbol | C_Small | C4 C7 C11 C13 C15 C21 C22 | 100nF | C_0603_1608Metric_Pad1.05x0.95mm_HandSolder | 7 | EMK107B7104KAHT
3 | Unpolarized capacitor, small symbol | C_Small | C19 | 10n | C_0603_1608Metric_Pad1.05x0.95mm_HandSolder | 1 | 06033C103K4T2A
4 | Unpolarized capacitor, small symbol | C_Small | C1 C2 C6 C10 C14 C18 | 10uF | C_0805_2012Metric_Pad1.15x1.40mm_HandSolder | 6 | C2012X7R1A106M125AC
5 | Unpolarized capacitor, small symbol | C_Small | C8 C9 C12 C16 C17 C20 C23 C24 C25 C26 | 1uF | C_0603_1608Metric_Pad1.05x0.95mm_HandSolder | 10 | LMK107B7105MA-T
6 | Unpolarized capacitor, small symbol | C_Small | C3 C5 | 2.2uF | C_0805_2012Metric_Pad1.15x1.40mm_HandSolder | 2 | LMK212B7225KG-T
7 | Switching Voltage Regulators Step-up DC/DC Reg 1 MHz, 1.6A, 5Vout | MCP1642B-50I_MS | IC1 IC2 | MCP1642B-50I_MS | SOP65P490X110-8N | 2 | MCP1642B-50I/MS
8 |  | Conector_PCB_A-B | J2 | Conector_PCB_A-B | Conector_PCB_A-B | 3 | CES-103-01-T-S
9 |  | Conector_PCB_A-B | J2 | Conector_PCB_A-B | Conector_PCB_A-B | 2 | CES-104-01-T-S
10 |  | Conector_PCB_B-C | J1 | Conector_PCB_B-C | Conector_PCB_B-C_Lado_B | 2 | 10132798-022100LF
11 | Inductor with iron core | L_Core_Iron | L2 | 1uH | L_0805_2012Metric_Pad1.15x1.40mm_HandSolder | 1 | LQM21PN1R0MC0D
12 | Inductor with iron core | L_Core_Iron | L1 L3 | 4.7uH | SRN3010TA-4R7M | 2 | SRN3010TA-4R7M
13 |  | Spacer | M1 M2 M3 | Spacer | Empty_Footprint | 3 | R30-3011202
14 | Resistor | R | R16 | 100k | R_0603_1608Metric_Pad1.05x0.95mm_HandSolder | 1 | RC0603JR-07100KL
15 | Resistor | R | R18 R19 R20 R21 | 10k | C_0603_1608Metric_Pad1.05x0.95mm_HandSolder | 4 | RC0603JR-0710KL
16 | Resistor | R | R17 | 10m | R_2512_6332Metric_Pad1.52x3.35mm_HandSolder | 1 | KRL3264-C-R010-F-T1
17 | Resistor | R | R2 | 120m | R_1206_3216Metric_Pad1.42x1.75mm_HandSolder | 1 | KRL1632E-M-R120-F-T5
18 | Resistor | R | R5 | 150k | R_0603_1608Metric_Pad1.05x0.95mm_HandSolder | 1 | RC0603FR-07150KL
19 | Resistor | R | R14 | 1k8 | R_0603_1608Metric_Pad1.05x0.95mm_HandSolder | 1 | RC0603FR-071K8L
20 | Resistor | R | R7 | 200m | R_1206_3216Metric_Pad1.42x1.75mm_HandSolder | 1 | KRL1632E-C-R200-F-T5
21 | Resistor | R | R9 | 22k | R_0603_1608Metric_Pad1.05x0.95mm_HandSolder | 1 | RC0603FR-1322KL
22 | Resistor | R | R4 R15 | 2k | R_0603_1608Metric_Pad1.05x0.95mm_HandSolder | 2 | RC0603FR-102KL
23 | Resistor | R | R10 | 39k | R_0603_1608Metric_Pad1.05x0.95mm_HandSolder | 1 | RC0603FR-1339KL
24 | Resistor | R | R1 R3 R6 R8 R11 R13 | 51R | R_0603_1608Metric_Pad1.05x0.95mm_HandSolder | 6 | AC0603FR-0751RL
25 | Resistor | R | R12 | 51m | R_1206_3216Metric_Pad1.42x1.75mm_HandSolder | 1 | KRL1632E-C-R051-F-T1
26 | 3MHz switching bucK regulator, 600mA 3.3V output voltage, | ADP2108AUJ-3.3 | U2 | ADP2108AUJ-3.3 | TSOT-23-5 | 1 | ADP2108AUJZ-3.3-R7
27 | Texas Instruments BQ24091DGQT, Battery Charge Controller, 1000mA, 10-Pin MSOP | BQ24091DGQT | U8 | BQ24091DGQT | SOP50P490X110-11N | 1 | BQ24091DGQT
28 | System Side Li Ion/Polymer Fuel Gauge, 4.2V, PDSON-12 | BQ27441DRZR-G1A | U9 | BQ27441DRZR-G1A | Texas_S-PDSO-N12 | 1 | BQ27441DRZR-G1A
29 | Current Shunt Monitor âˆ’16 V to +80 V Common-Mode Range, 50V/V, SOT-23-5 | INA194 | U3 U5 U7 | INA194 | SOT-23-5 | 3 | INA194AIDBVR
30 | 1MHz, Low-Power Op Amp, SOT-23-5 | MCP6001-OT | U4 U6 | MCP6001-OT | SOT-23-5 | 2 | MCP6001T-I/OT
31 | Micrel MIC5323-3.3YD5 TR, LDO Voltage Regulator, 300mA, 3.3 V 2%, 2.65 5.5 Vin,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 | MIC5323-3.3YD5_TR | U1 | MIC5323-3.3YD5_TR | SOT95P280X100-5N | 1 | MIC5323-3.3YD5 TR
